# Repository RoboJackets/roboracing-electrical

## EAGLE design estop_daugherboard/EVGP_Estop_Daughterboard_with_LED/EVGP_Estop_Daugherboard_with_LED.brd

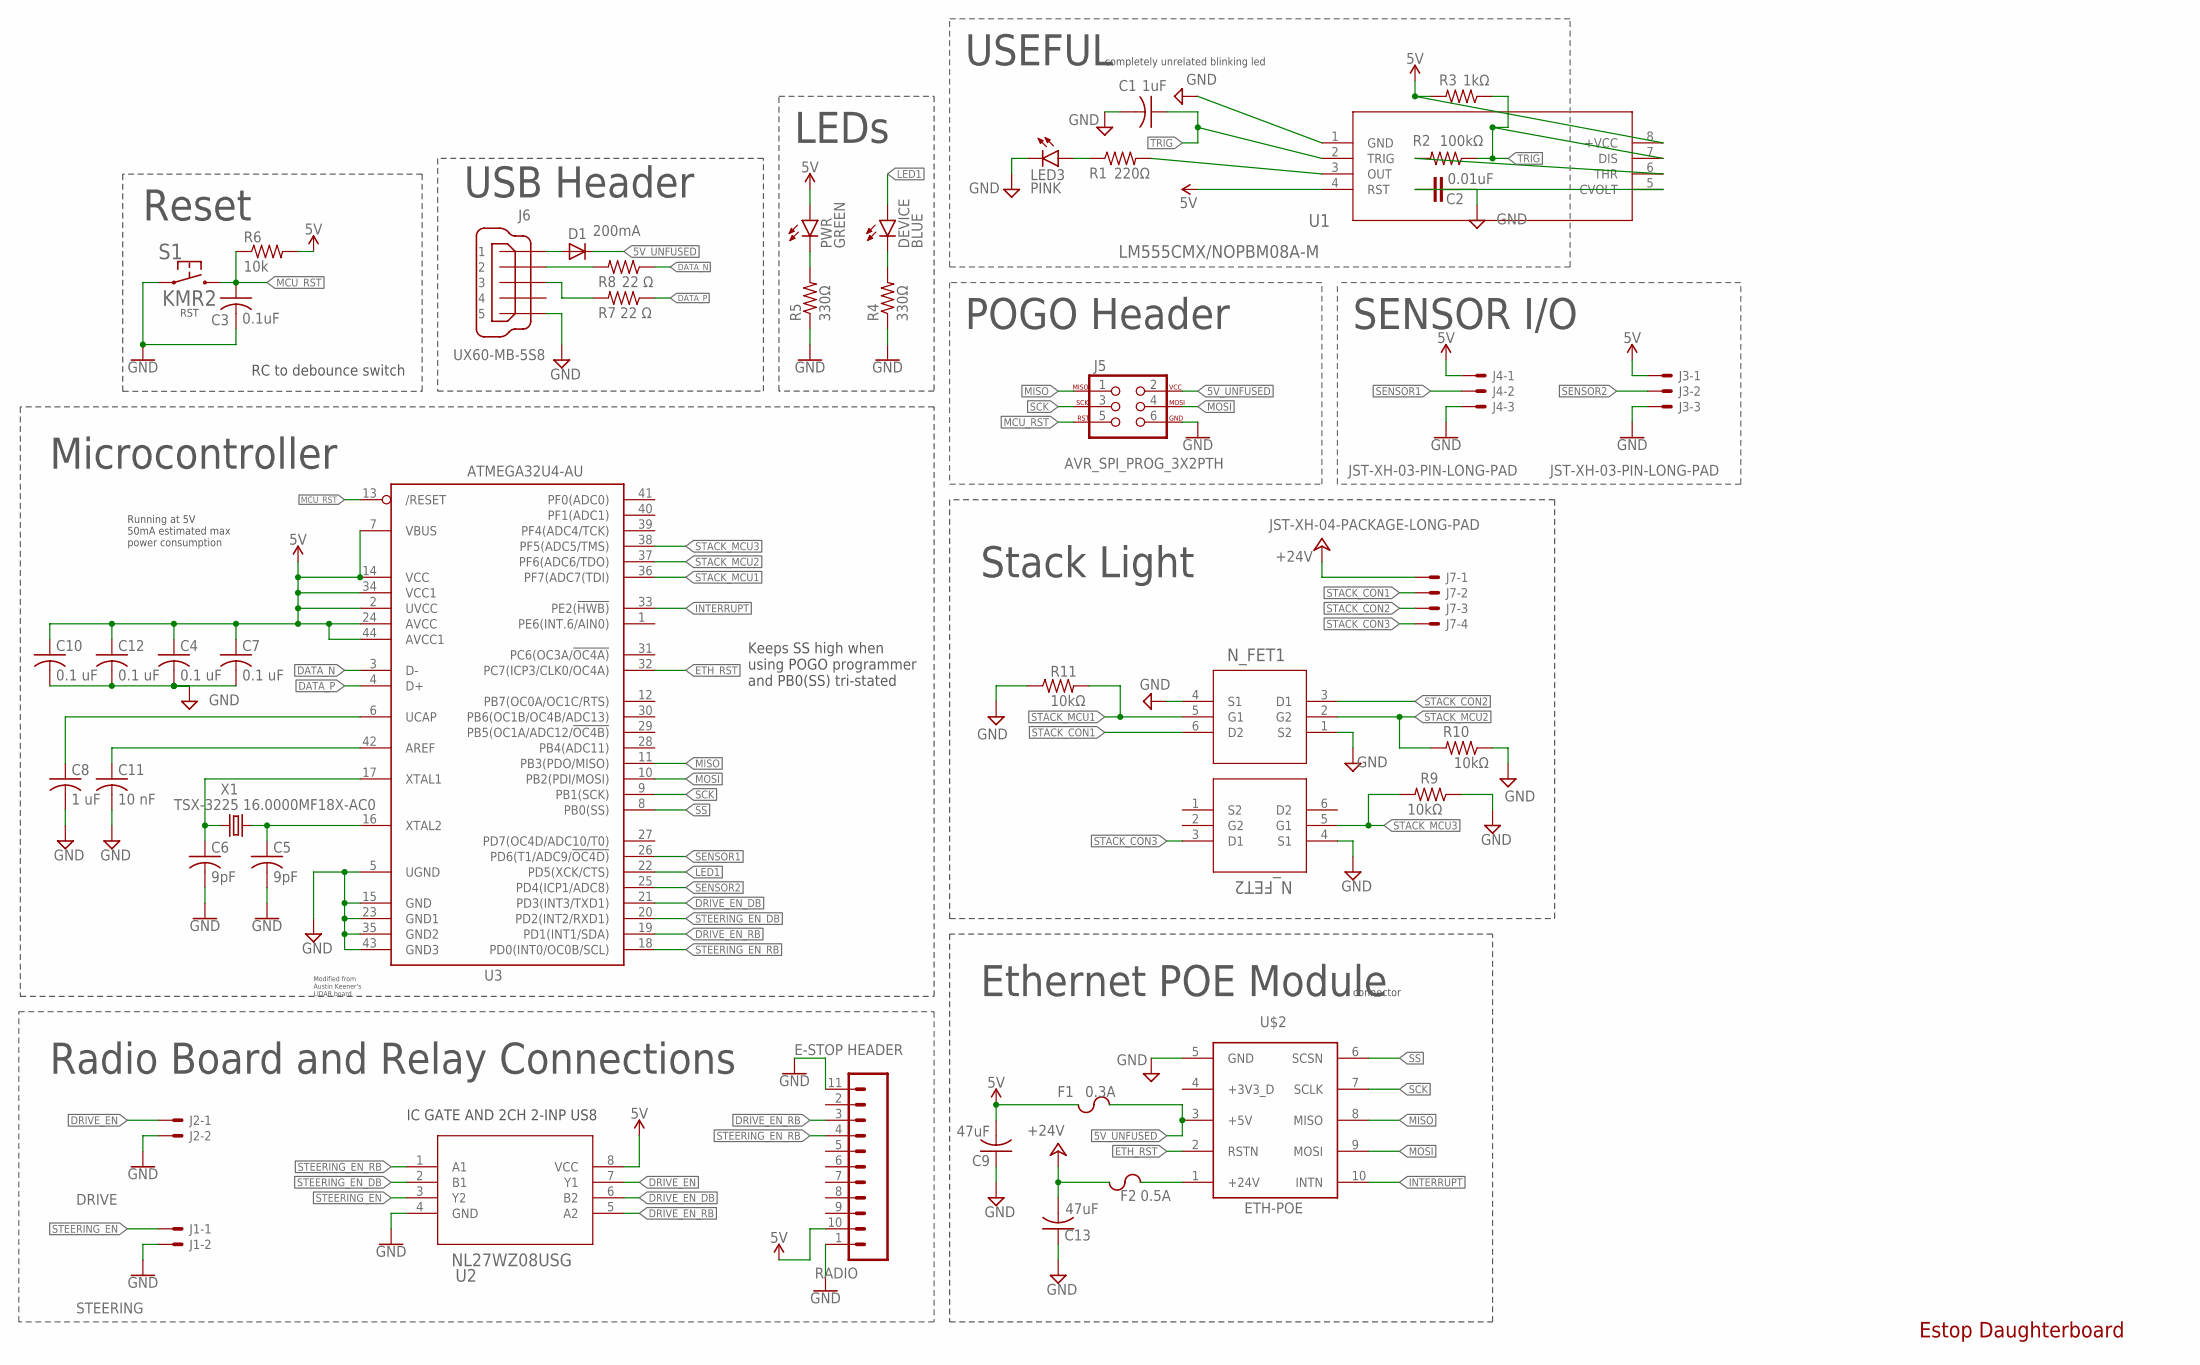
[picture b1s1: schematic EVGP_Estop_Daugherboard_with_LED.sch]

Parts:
C1: 1uF; C1206
C2: 0.01uF; C0603
C3: 0.1uF; C0603
C4, C7, C10, C12: 0.1 uF; C0603
C5, C6: 9pF; C0603
C8: 1 uF; C0603
C9, C13: 47uF; C1206
C11: 10 nF; C0603
D1: 200mA; SOD323-R
DEVICE: BLUE; CHIP-LED0603
F1: 0.3A; F1206
F2: 0.5A; F1206
J1: STEERING; JST-XH-02-PACKAGE-LONG-PAD
J2: DRIVE; JST-XH-02-PACKAGE-LONG-PAD
J3, J4: JST-XH-03-PIN-LONG-PAD; JST-XH-03-PACKAGE-LONG-PAD
J5: AVR_SPI_PROG_3X2PTH; 2X3
J6: UX60-MB-5S8
J7: JST-XH-04-PACKAGE-LONG-PAD
LED3: PINK; CHIP-LED0603
PWR: GREEN; CHIP-LED0603
Q1: N_FET2; SOT-363
Q2: N_FET1; SOT-363
R1: 220Ω; R0603
R2: 100kΩ; R0603
R3: 1kΩ; R0603
R4, R5: 330Ω; R0603
R6: 10k; R0603
R7, R8: 22 Ω; R0603
R9, R10, R11: 10kΩ; R0603
RADIO: E-STOP HEADER; RADIO_V1.3
S1: KMR2
U1: LM555CMX/NOPBM08A-M; M08A-M
U2: NL27WZ08USG; US8_2P40X2P10
U3: ATMEGA32U4-AU; TQFP44
U$2: ETH-POE; HDRVR10W64P4000X254_2X5_1016X508X254B
X1: TSX-3225 16.0000MF18X-AC0; XTAL-3.2X2.5

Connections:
5V: C4.1, C7.1, C9.2, C10.1, C12.1, F1.1, J3.1, J4.1, PWR.A, R3.2, R6.2, RADIO.10 (5V), U1.4 (RST), U1.8 (+VCC), U2.8 (VCC), U3.2 (UVCC), U3.7 (VBUS), U3.14 (VCC), U3.24 (AVCC), U3.34 (VCC1), U3.44 (AVCC1)
5V_UNFUSED: D1.C, F1.2, J5.2, U$2.3 (+5V)
24V_UNFUSED: F2.2, U$2.1 (+24V)
+24V: C13.2, F2.1, J7.1
AREF: C11.1, U3.42 (AREF)
DATA_N: R8.1, U3.3 (D-)
DATA_P: R7.1, U3.4 (D+)
DRIVE_EN: J2.1, U2.7 (Y1)
DRIVE_EN_DB: U2.6 (B2), U3.21 (PD3(INT3/TXD1))
DRIVE_EN_RB: RADIO.3 (D1), U2.5 (A2), U3.19 (PD1(INT1/SDA))
ETH_RST: U3.32 (PC7(ICP3/CLK0/OC4A)), U$2.2 (RSTN)
GND: C1.2, C2.2, C3.2, C4.2, C5.2, C6.2, C7.2, C8.2, C9.1, C10.2, C11.2, C12.2, C13.1, J1.2, J2.2, J3.3, J4.3, J5.6, J6.5, LED3.C, Q1.4 (S1), Q2.1 (S2), Q2.4 (S1), R4.1, R5.1, R9.1, R10.1, R11.1, RADIO.1 (GND), RADIO.11 (GND), S1.1.1 (1), S1.1.2 (1), U1.1 (GND), U2.4 (GND), U3.5 (UGND), U3.15 (GND), U3.23 (GND1), U3.35 (GND2), U3.43 (GND3), U$2.5 (GND)
INTERRUPT: U3.33 (PE2(!HWB)), U$2.10 (INTN)
LED1: DEVICE.A, U3.22 (PD5(XCK/CTS))
MCU_RST: C3.1, J5.5, R6.1, S1.2.1 (2), S1.2.2 (2), U3.13 (/RESET)
MISO: J5.1, U3.11 (PB3(PDO/MISO)), U$2.8 (MISO)
MOSI: J5.4, U3.10 (PB2(PDI/MOSI)), U$2.9 (MOSI)
unnamed: LED3.A, R1.1
unnamed: R2.2, U1.6 (THR)
unnamed: PWR.C, R5.2
unnamed: C2.1, U1.5 (CVOLT)
unnamed: J6.2, R8.2
unnamed: DEVICE.C, R4.2
unnamed: D1.A, J6.1
unnamed: R1.2, U1.3 (OUT)
unnamed: J6.3, R7.2
SCK: J5.3, U3.9 (PB1(SCK)), U$2.7 (SCLK)
SENSOR1: J4.2, U3.26 (PD6(T1/ADC9/!OC4D))
SENSOR2: J3.2, U3.25 (PD4(ICP1/ADC8))
SS: U3.8 (PB0(SS)), U$2.6 (SCSN)
STACK_CON1: J7.2, Q2.6 (D2)
STACK_CON2: J7.3, Q2.3 (D1)
STACK_CON3: J7.4, Q1.3 (D1)
STACK_MCU1: Q2.5 (G1), R11.2, U3.36 (PF7(ADC7(TDI))
STACK_MCU2: Q2.2 (G2), R10.2, U3.37 (PF6(ADC6/TDO))
STACK_MCU3: Q1.5 (G1), R9.2, U3.38 (PF5(ADC5/TMS))
STEERING_EN: J1.1, U2.3 (Y2)
STEERING_EN_DB: U2.2 (B1), U3.20 (PD2(INT2/RXD1))
STEERING_EN_RB: RADIO.4 (D2), U2.1 (A1), U3.18 (PD0(INT0/OC0B/SCL))
TRIG: C1.1, R2.1, R3.1, U1.2 (TRIG), U1.7 (DIS)
UCAP: C8.1, U3.6 (UCAP)
XTAL1: C6.1, U3.17 (XTAL1), X1.1
XTAL2: C5.1, U3.16 (XTAL2), X1.3 (2)

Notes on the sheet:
Modified from Austin Keener's LIDAR board
POGO Header
RC to debounce switch
Reset
LEDs
Running at 5V 50mA estimated max power consumption
Microcontroller
USB Header
Keeps SS high when using POGO programmer and PB0(SS) tri-stated
Radio Board and Relay Connections
IC GATE AND 2CH 2-INP US8
SENSOR I/O
Stack Light
Ethernet POE Module
connector
Estop Daughterboard
USEFUL
completely unrelated blinking led

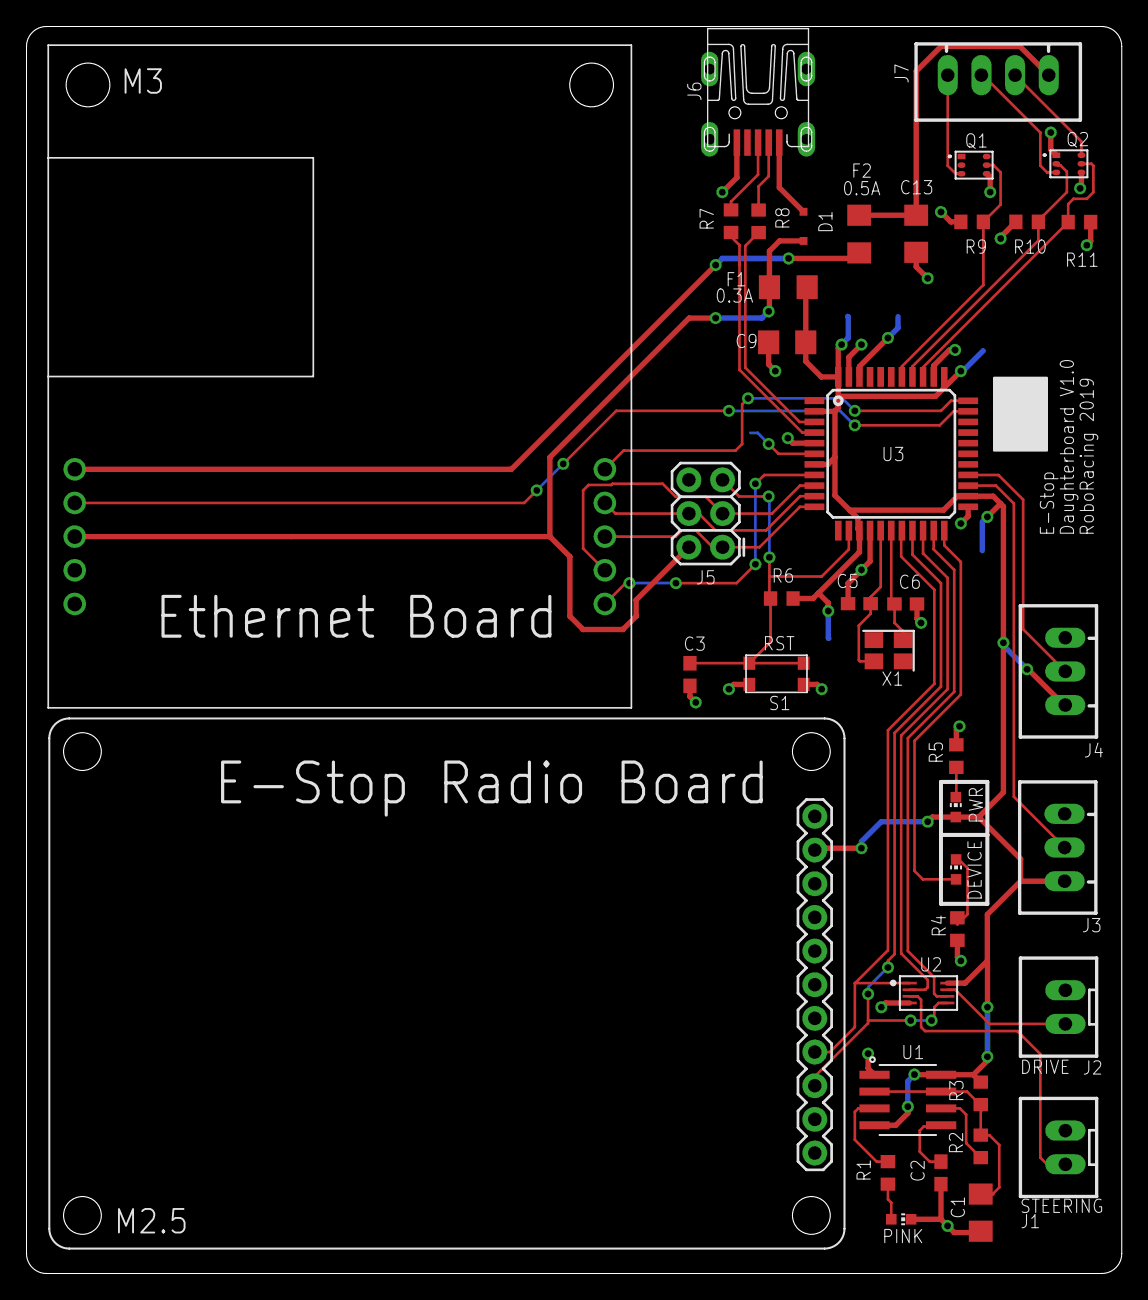
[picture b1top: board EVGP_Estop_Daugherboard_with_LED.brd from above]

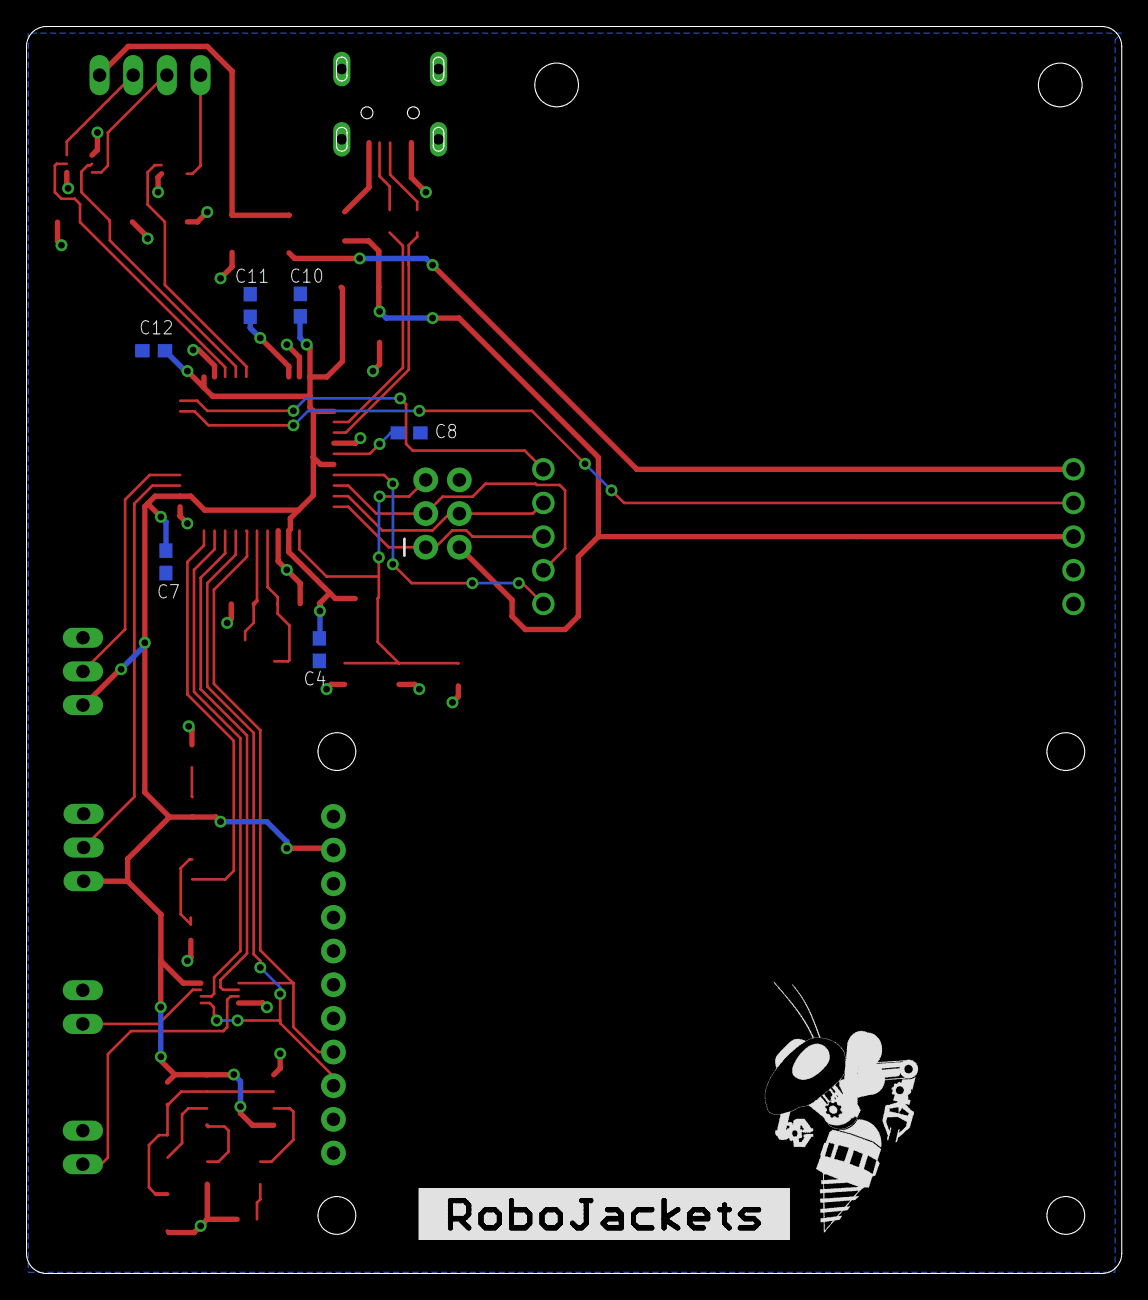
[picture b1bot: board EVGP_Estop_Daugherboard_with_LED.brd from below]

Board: 2 copper layers, 82.6 x 94.1 mm, 48 parts (8 on the bottom side), 43 nets.

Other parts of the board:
U$1: ROBOBUZZ_1.0X
U$3: ROBOJACKETS

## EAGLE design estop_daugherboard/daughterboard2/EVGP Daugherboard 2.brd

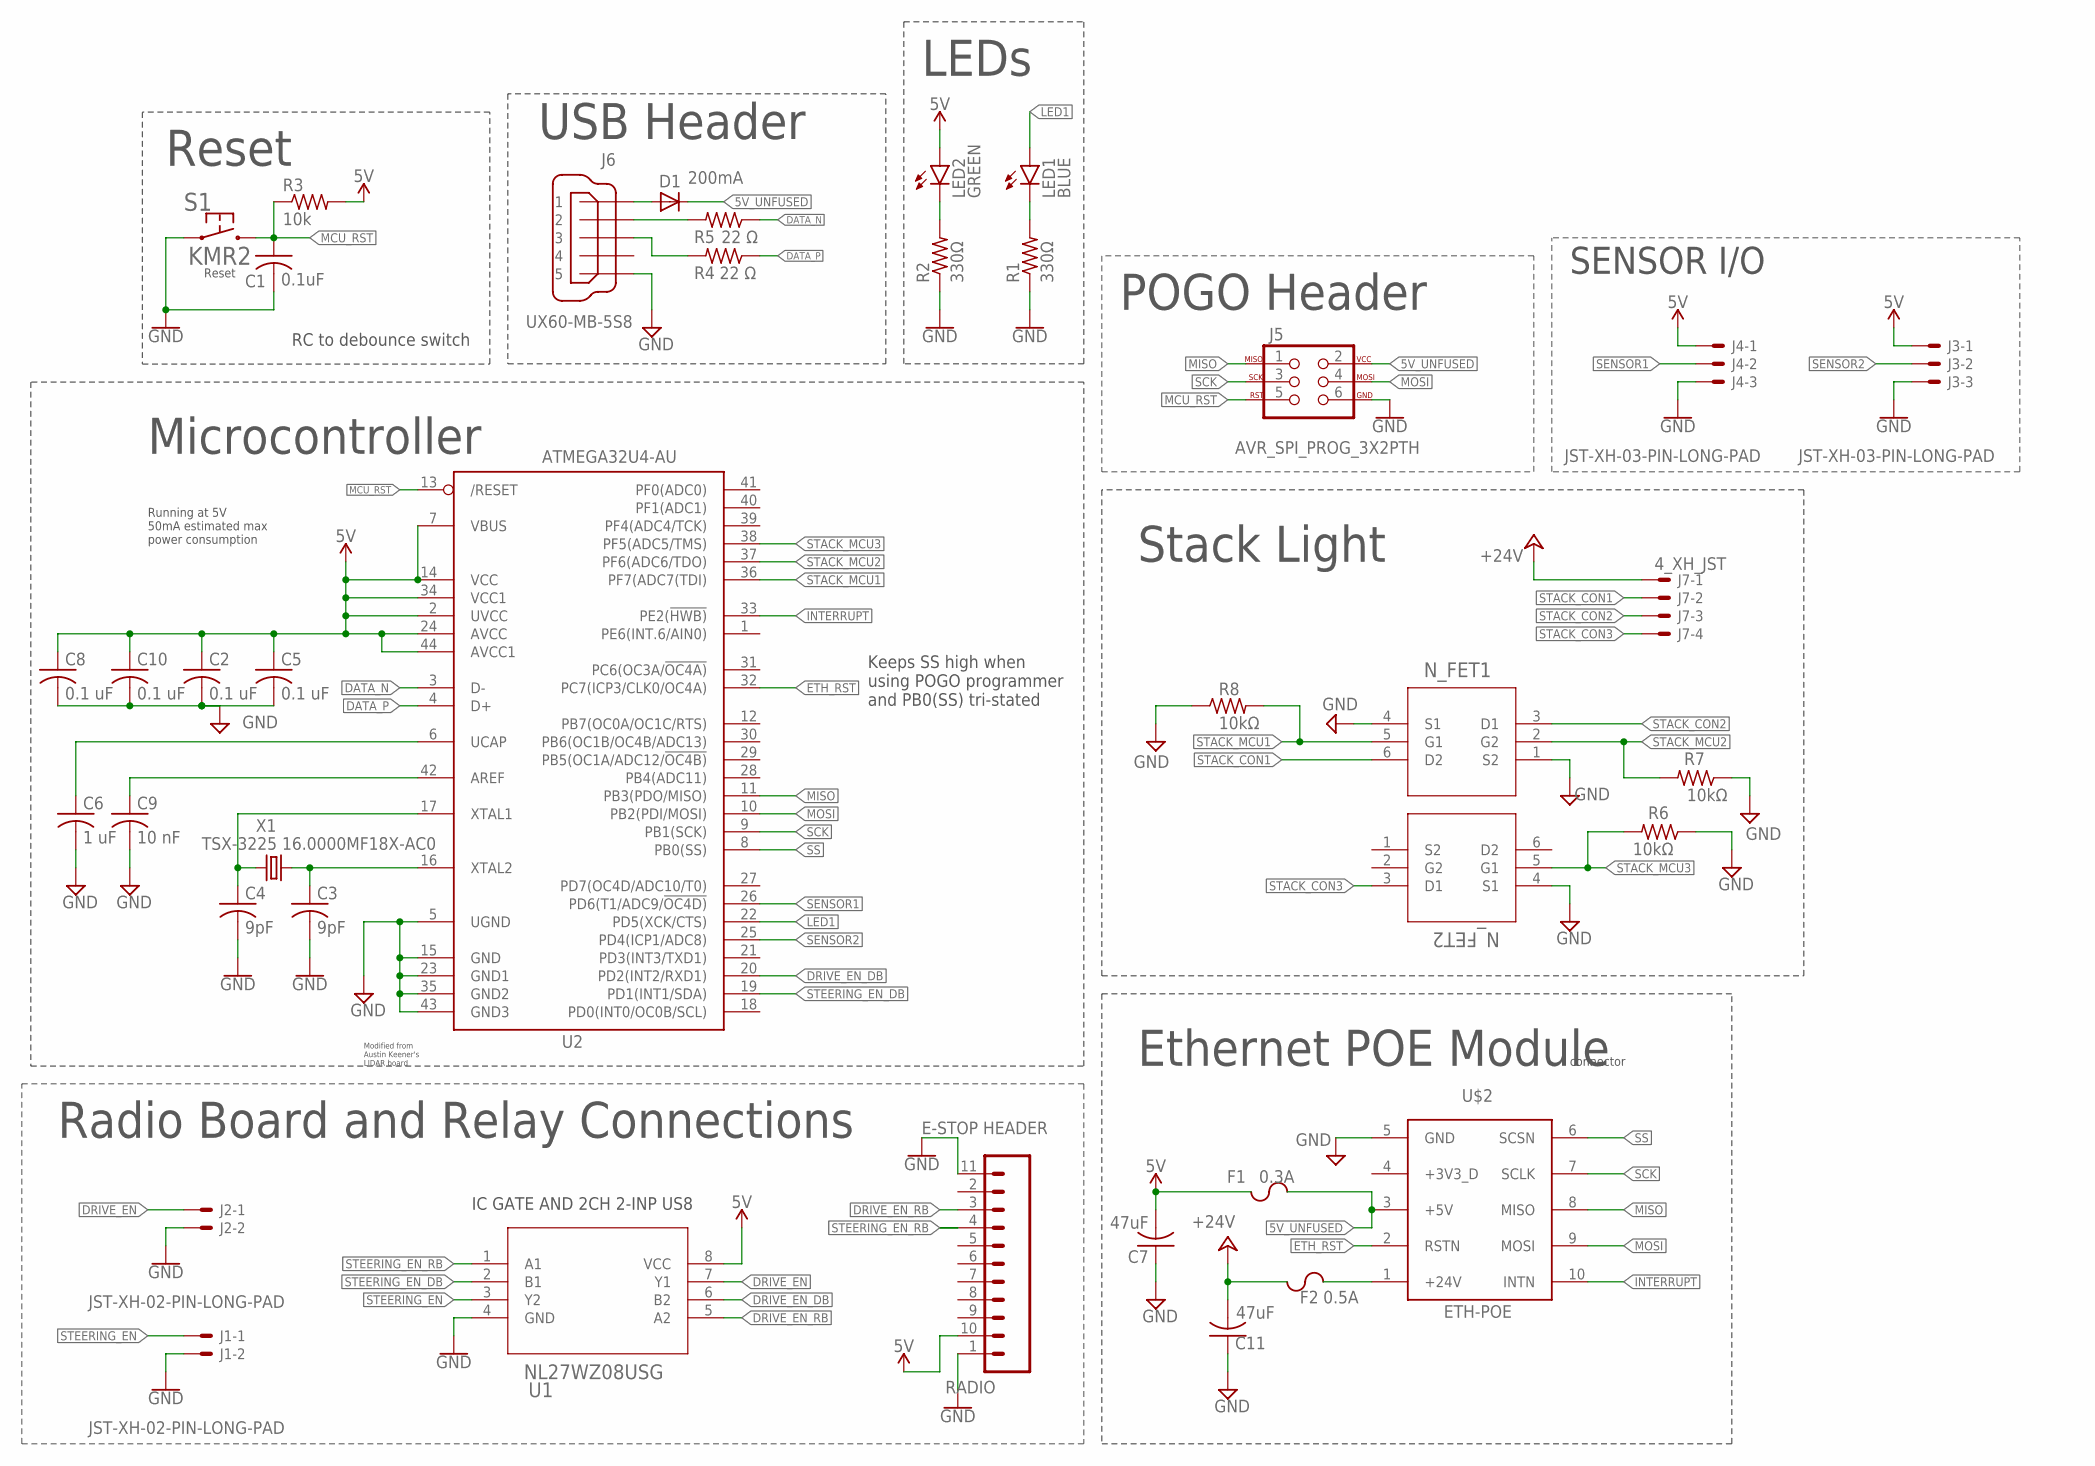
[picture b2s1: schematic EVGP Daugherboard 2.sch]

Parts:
C1: 0.1uF; C0603
C2, C5, C8, C10: 0.1 uF; C0603
C3, C4: 9pF; C0603
C6: 1 uF; C0603
C7, C11: 47uF; C1206
C9: 10 nF; C0603
D1: 200mA; SOD323-R
F1: 0.3A; F1206
F2: 0.5A; F1206
J1, J2: JST-XH-02-PIN-LONG-PAD; JST-XH-02-PACKAGE-LONG-PAD
J3, J4: JST-XH-03-PIN-LONG-PAD; JST-XH-03-PACKAGE-LONG-PAD
J5: AVR_SPI_PROG_3X2PTH; 2X3
J6: UX60-MB-5S8
J7: 4_XH_JST; JST-XH-04-PACKAGE-LONG-PAD
LED1: BLUE; CHIP-LED0603
LED2: GREEN; CHIP-LED0603
Q1: N_FET2; SOT-363
Q2: N_FET1; SOT-363
R1, R2: 330Ω; R0603
R3: 10k; R0603
R4, R5: 22 Ω; R0603
R6, R7, R8: 10kΩ; R0603
RADIO: E-STOP HEADER; RADIO_V1.3
S1: KMR2
U1: NL27WZ08USG; US8_2P40X2P10
U2: ATMEGA32U4-AU; TQFP44
U$2: ETH-POE; HDRVR10W64P4000X254_2X5_1016X508X254B
X1: TSX-3225 16.0000MF18X-AC0; XTAL-3.2X2.5

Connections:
5V: C2.1, C5.1, C7.2, C8.1, C10.1, F1.1, J3.1, J4.1, LED2.A, R3.2, RADIO.10 (5V), U1.8 (VCC), U2.2 (UVCC), U2.7 (VBUS), U2.14 (VCC), U2.24 (AVCC), U2.34 (VCC1), U2.44 (AVCC1)
5V_UNFUSED: D1.C, F1.2, J5.2, U$2.3 (+5V)
24V_UNFUSED: F2.2, U$2.1 (+24V)
+24V: C11.2, F2.1, J7.1
AREF: C9.1, U2.42 (AREF)
DATA_N: R5.1, U2.3 (D-)
DATA_P: R4.1, U2.4 (D+)
DRIVE_EN: J2.1, U1.7 (Y1)
DRIVE_EN_DB: U1.6 (B2), U2.20 (PD2(INT2/RXD1))
DRIVE_EN_RB: RADIO.3 (D1), U1.5 (A2)
ETH_RST: U2.32 (PC7(ICP3/CLK0/OC4A)), U$2.2 (RSTN)
GND: C1.2, C2.2, C3.2, C4.2, C5.2, C6.2, C7.1, C8.2, C9.2, C10.2, C11.1, J1.2, J2.2, J3.3, J4.3, J5.6, J6.5, Q1.4 (S1), Q2.1 (S2), Q2.4 (S1), R1.1, R2.1, R6.1, R7.1, R8.1, RADIO.1 (GND), RADIO.11 (GND), S1.1.1 (1), S1.1.2 (1), U1.4 (GND), U2.5 (UGND), U2.15 (GND), U2.23 (GND1), U2.35 (GND2), U2.43 (GND3), U$2.5 (GND)
INTERRUPT: U2.33 (PE2(!HWB)), U$2.10 (INTN)
LED1: LED1.A, U2.22 (PD5(XCK/CTS))
MCU_RST: C1.1, J5.5, R3.1, S1.2.1 (2), S1.2.2 (2), U2.13 (/RESET)
MISO: J5.1, U2.11 (PB3(PDO/MISO)), U$2.8 (MISO)
MOSI: J5.4, U2.10 (PB2(PDI/MOSI)), U$2.9 (MOSI)
unnamed: LED2.C, R2.2
unnamed: J6.2, R5.2
unnamed: LED1.C, R1.2
unnamed: D1.A, J6.1
unnamed: J6.3, R4.2
SCK: J5.3, U2.9 (PB1(SCK)), U$2.7 (SCLK)
SENSOR1: J4.2, U2.26 (PD6(T1/ADC9/!OC4D))
SENSOR2: J3.2, U2.25 (PD4(ICP1/ADC8))
SS: U2.8 (PB0(SS)), U$2.6 (SCSN)
STACK_CON1: J7.2, Q2.6 (D2)
STACK_CON2: J7.3, Q2.3 (D1)
STACK_CON3: J7.4, Q1.3 (D1)
STACK_MCU1: Q2.5 (G1), R8.2, U2.36 (PF7(ADC7(TDI))
STACK_MCU2: Q2.2 (G2), R7.2, U2.37 (PF6(ADC6/TDO))
STACK_MCU3: Q1.5 (G1), R6.2, U2.38 (PF5(ADC5/TMS))
STEERING_EN: J1.1, U1.3 (Y2)
STEERING_EN_DB: U1.2 (B1), U2.19 (PD1(INT1/SDA))
STEERING_EN_RB: RADIO.4 (D2), U1.1 (A1)
UCAP: C6.1, U2.6 (UCAP)
XTAL1: C4.1, U2.17 (XTAL1), X1.1
XTAL2: C3.1, U2.16 (XTAL2), X1.3 (2)

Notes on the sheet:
Modified from Austin Keener's LIDAR board
POGO Header
RC to debounce switch
Reset
LEDs
Running at 5V 50mA estimated max power consumption
Microcontroller
USB Header
Keeps SS high when using POGO programmer and PB0(SS) tri-stated
Radio Board and Relay Connections
IC GATE AND 2CH 2-INP US8
SENSOR I/O
Stack Light
Ethernet POE Module
connector

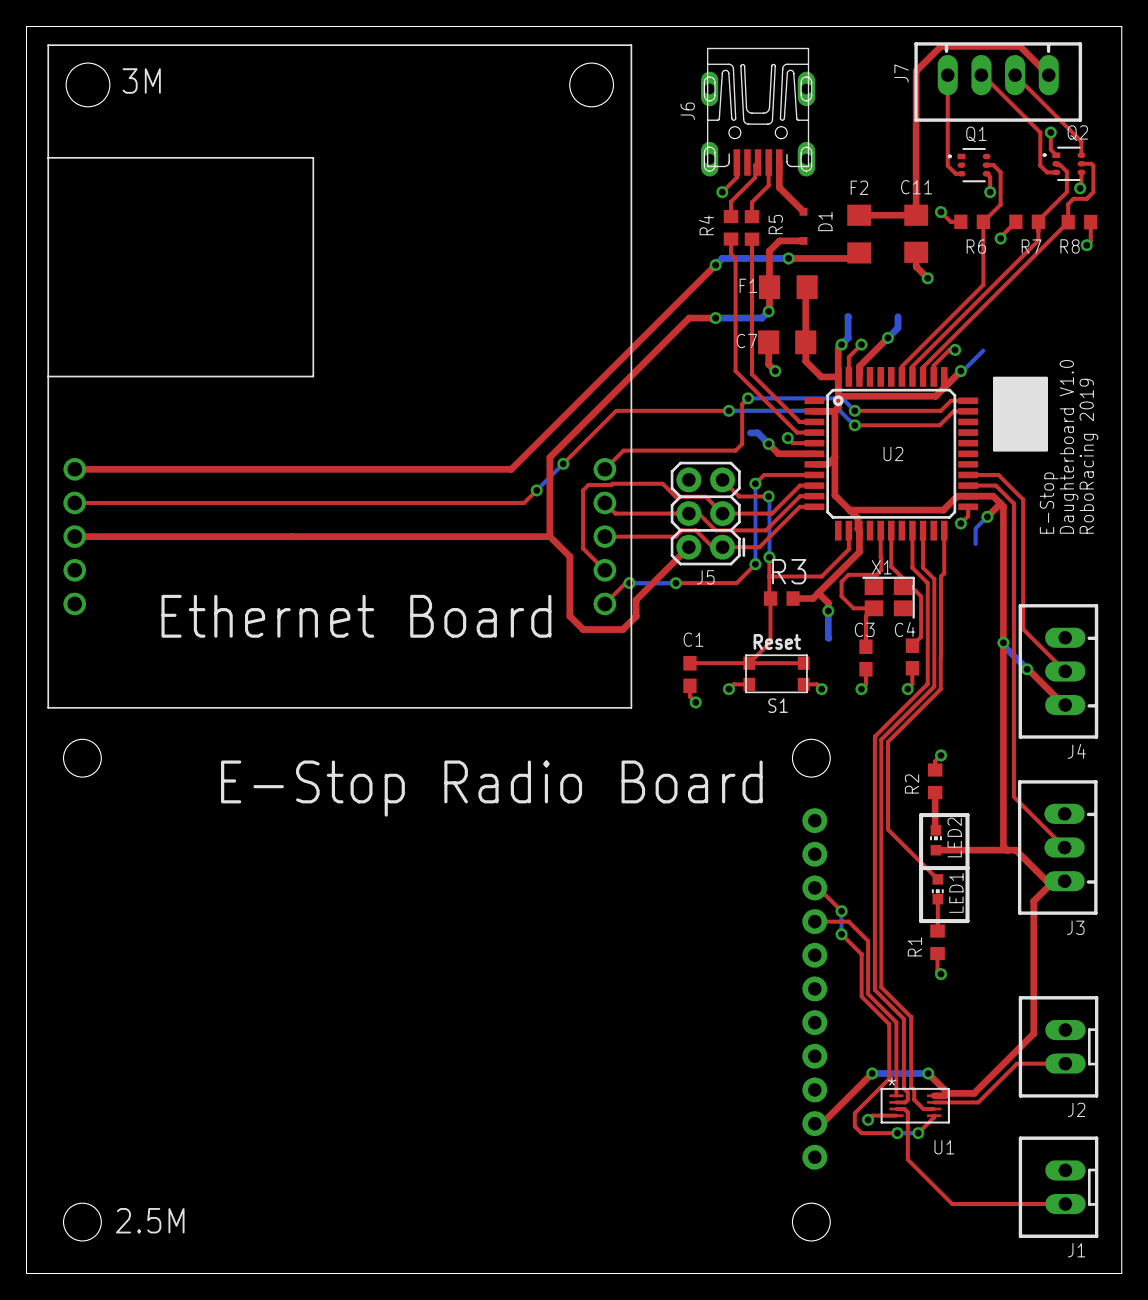
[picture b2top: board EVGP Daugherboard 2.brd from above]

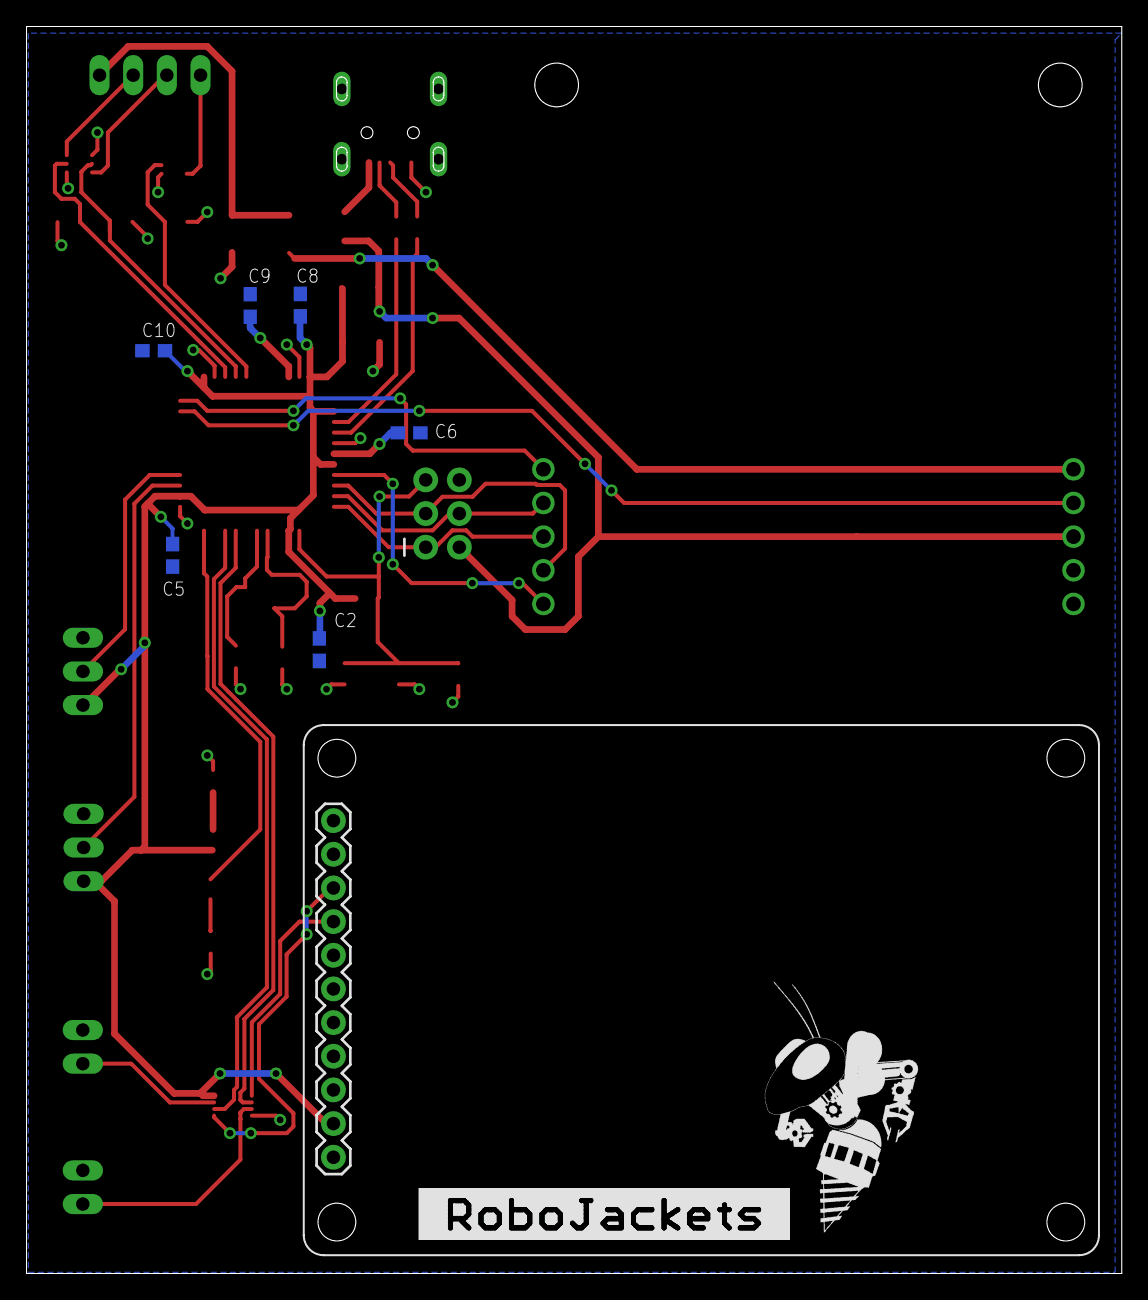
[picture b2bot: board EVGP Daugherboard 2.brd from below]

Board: 2 copper layers, 82.6 x 94.1 mm, 41 parts (9 on the bottom side), 38 nets.

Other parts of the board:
U$1: ROBOBUZZ_1.0X
U$3: ROBOJACKETS

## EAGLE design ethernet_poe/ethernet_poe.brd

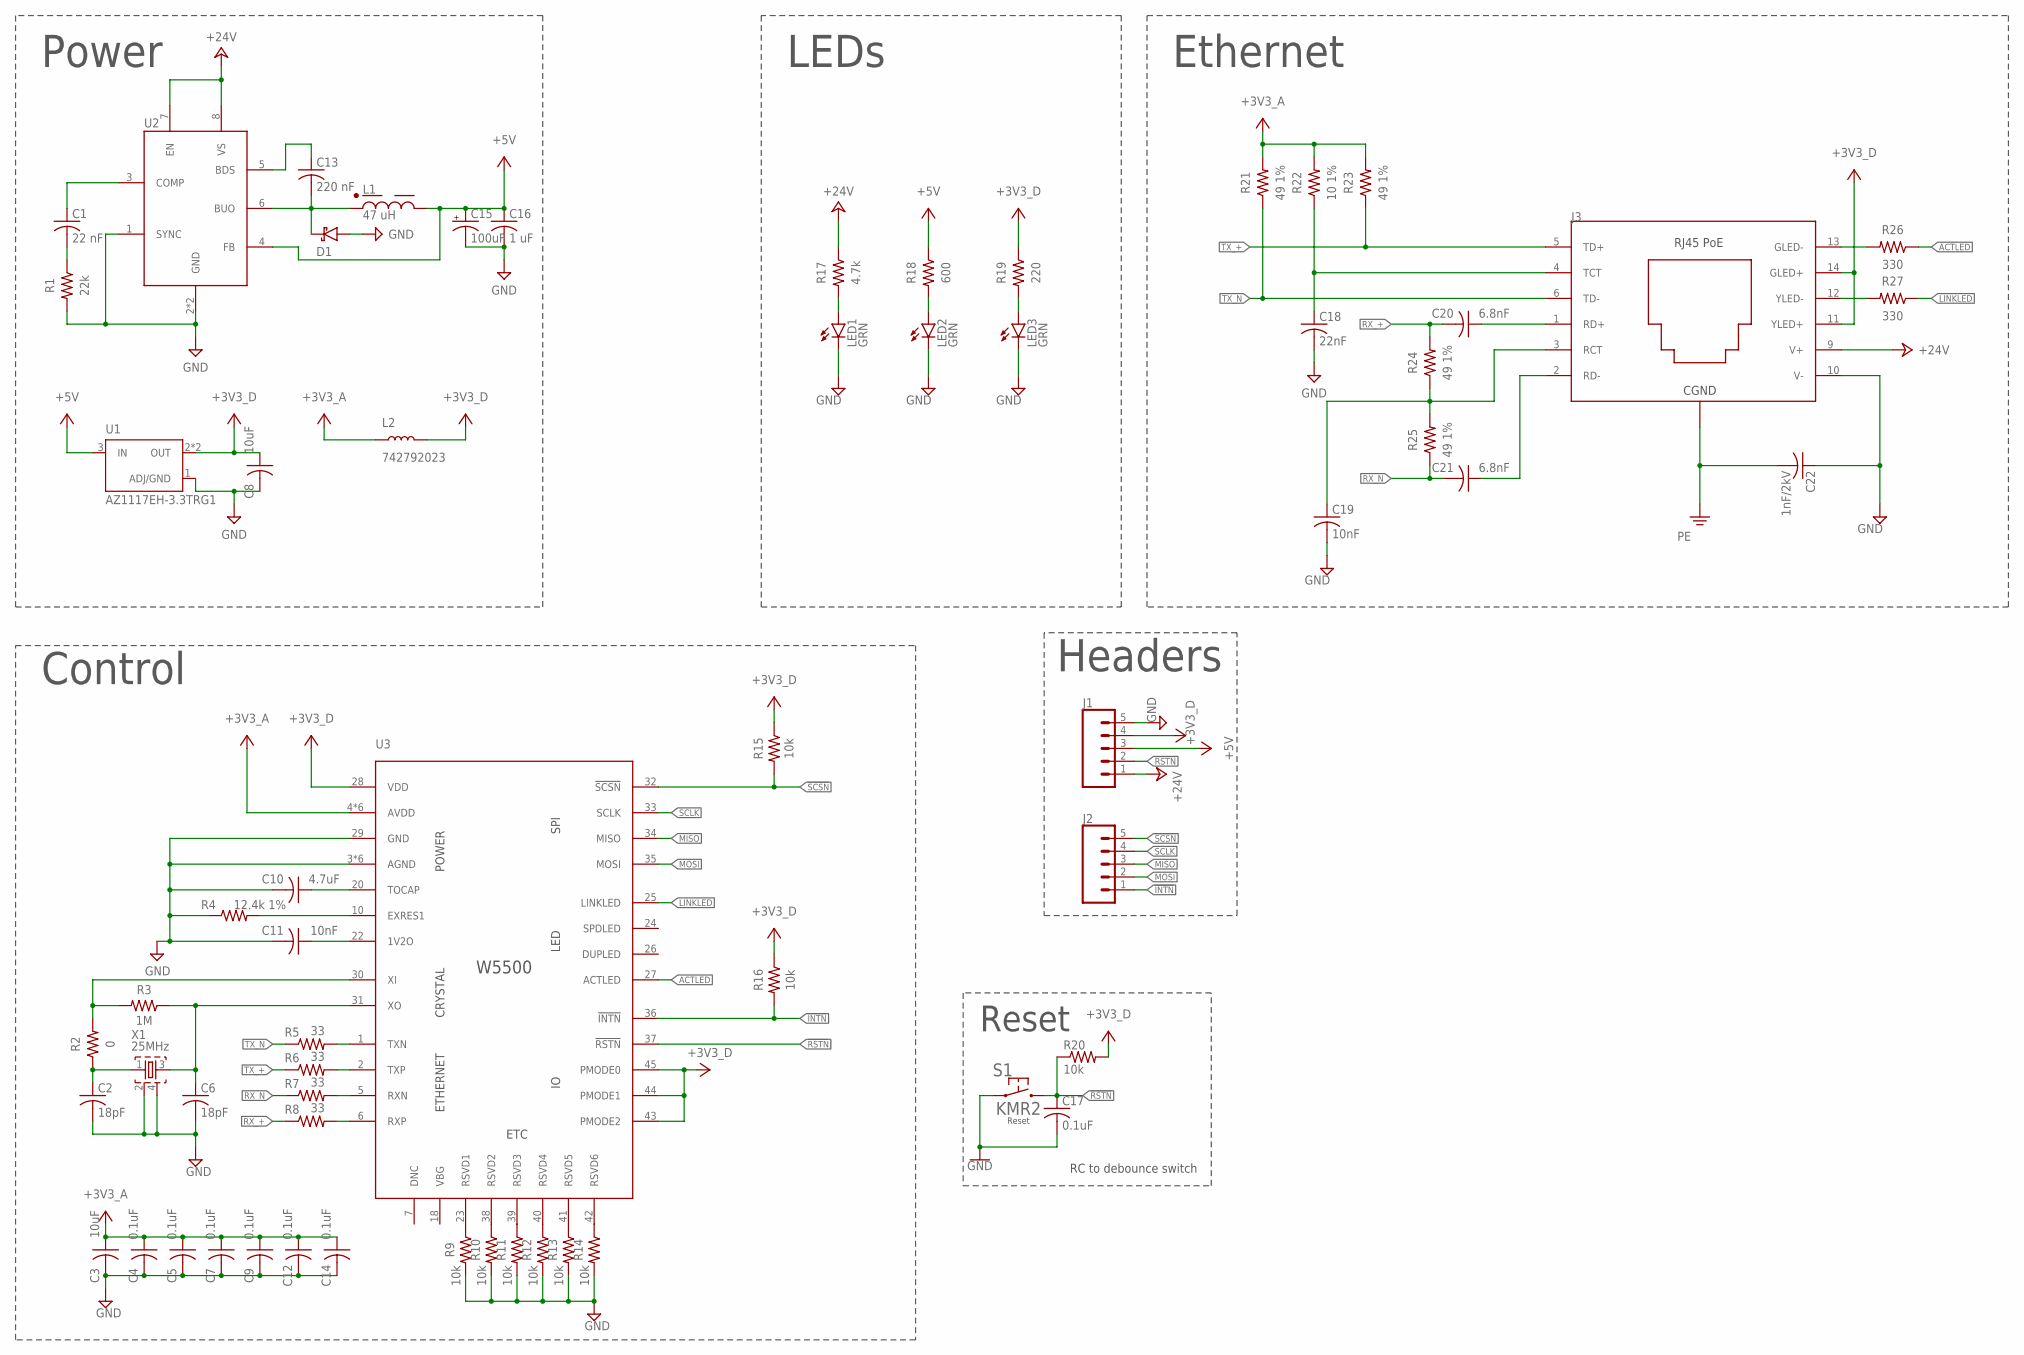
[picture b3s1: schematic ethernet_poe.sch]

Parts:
C1: 22 nF; C0603
C2, C6: 18pF; C0603
C3, C8: 10uF; C0603
C4, C5, C7, C9, C12, C14, C17: 0.1uF; C0603
C10: 4.7uF; C0603
C11, C19: 10nF; C0603
C13: 220 nF; C0603
C15: 100uF; E2-5
C16: 1 uF; C0603
C18: 22nF; C0603
C20, C21: 6.8nF; C0603
C22: 1nF/2kV; C1206
D1: SCHOTTKYSOD-323; SOD-323
J1, J2: CONN_05; 1X05
J3: ARJP11A; ARJP11A-MBSB-A-B-EMU2
L1: 47 uH; 744771147
L2: 742792023; 0805
LED1, LED2, LED3: GRN; CHIP-LED0603
R1: 22k; R0603
R2: 0; R0603
R3: 1M; R0603
R4: 12.4k 1%; R0603
R5, R6, R7, R8: 33; R0603
R9, R10, R11, R12, R13, R14, R15, R16, R20: 10k; R0603
R17: 4.7k; R0603
R18: 600; R0603
R19: 220; R0603
R21, R23, R24, R25: 49 1%; R0603
R22: 10 1%; R0603
R26, R27: 330; R0603
S1: KMR2
U1: AZ1117EH-3.3TRG1; SOT230P700X180-4N
U2: IFX91041; SOIC-8-EXPOSED_PAD
U3: W5500; 48-LQFP
X1: 25MHz; OSCILLATOR-SMD-2.5X2

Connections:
3V3_LED: LED3.A, R19.2
5V_LED: LED2.A, R18.2
24V_LED: LED1.A, R17.2
!INTN: J2.1, R16.2, U3.36 (!INTN)
!RSTN: C17.1, J1.2, R20.1, S1.2.1 (2), S1.2.2 (2), U3.37 (!RSTN)
!SCSN: J2.5, R15.2, U3.32 (!SCSN)
+3V3_A: C3.1, C4.1, C5.1, C7.1, C9.1, C12.1, C14.1, L2.1, R21.2, R22.2, R23.2, U3.4 (AVDD), U3.8 (AVDD), U3.11 (AVDD), U3.15 (AVDD), U3.17 (AVDD), U3.21 (AVDD)
+3V3_D: C8.1, J1.4, J3.11 (YLED+), J3.14 (GLED+), L2.2, R15.1, R16.1, R19.1, R20.2, U1.2 (OUT), U1.4 (OUT), U3.28 (VDD), U3.43 (PMODE2), U3.44 (PMODE1), U3.45 (PMODE0)
+5V: C15.+, C16.1, J1.3, L1.1, R18.1, U1.3 (IN), U2.4 (FB)
+24V: J1.1, J3.9 (V+), R17.1, U2.7 (EN), U2.8 (VS)
ACTLED: R26.1, U3.27 (ACTLED)
GND: C2.2, C3.2, C4.2, C5.2, C6.2, C7.2, C8.2, C9.2, C10.2, C11.2, C12.2, C14.2, C15.-, C16.2, C17.2, C18.2, C19.2, C22.1, D1.A, J1.5, J3.10 (V-), LED1.C, LED2.C, LED3.C, R1.2, R4.1, R9.2, R10.2, R11.2, R12.2, R13.2, R14.2, S1.1.1 (1), S1.1.2 (1), U1.1 (ADJ/GND), U2.1 (SYNC), U2.2 (GND), U2.P$9 (GND), U3.3 (AGND), U3.9 (AGND), U3.14 (AGND), U3.16 (AGND), U3.19 (AGND), U3.29 (GND), U3.48 (AGND), X1.2 (SHD1), X1.4 (SHD2)
LINKLED: R27.1, U3.25 (LINKLED)
MISO: J2.3, U3.34 (MISO)
MOSI: J2.2, U3.35 (MOSI)
unnamed: R9.1, U3.23 (RSVD1)
unnamed: R10.1, U3.38 (RSVD2)
unnamed: R11.1, U3.39 (RSVD3)
unnamed: R5.2, U3.1 (TXN)
unnamed: R6.2, U3.2 (TXP)
unnamed: R12.1, U3.40 (RSVD4)
unnamed: R7.2, U3.5 (RXN)
unnamed: R8.2, U3.6 (RXP)
unnamed: C2.1, R2.1, X1.1 (IN)
unnamed: J3.12 (YLED-), R27.2
unnamed: C6.1, R3.1, U3.31 (XO), X1.3 (OUT)
unnamed: J3.13 (GLED-), R26.2
unnamed: R2.2, R3.2, U3.30 (XI)
unnamed: C13.2, D1.C, L1.P$2, U2.6 (BUO)
unnamed: C13.1, U2.5 (BDS)
unnamed: C1.2, R1.1
unnamed: C1.1, U2.3 (COMP)
unnamed: C11.1, U3.22 (1V2O)
unnamed: C10.1, U3.20 (TOCAP)
unnamed: R13.1, U3.41 (RSVD5)
unnamed: R4.2, U3.10 (EXRES1)
unnamed: R14.1, U3.42 (RSVD6)
PE: C22.2, J3.15 (CGND), J3.16 (CGND)
RCT: C19.1, J3.3 (RCT), R24.1, R25.2
RD_+: C20.1, J3.1 (RD+)
RD_N: C21.1, J3.2 (RD-)
RX_+: C20.2, R8.1, R24.2
RX_N: C21.2, R7.1, R25.1
SCLK: J2.4, U3.33 (SCLK)
TCT: C18.1, J3.4 (TCT), R22.1
TX_+: J3.5 (TD+), R6.1, R23.1
TX_N: J3.6 (TD-), R5.1, R21.1

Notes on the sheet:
Power
Control
LEDs
Ethernet
Headers
RC to debounce switch
Reset

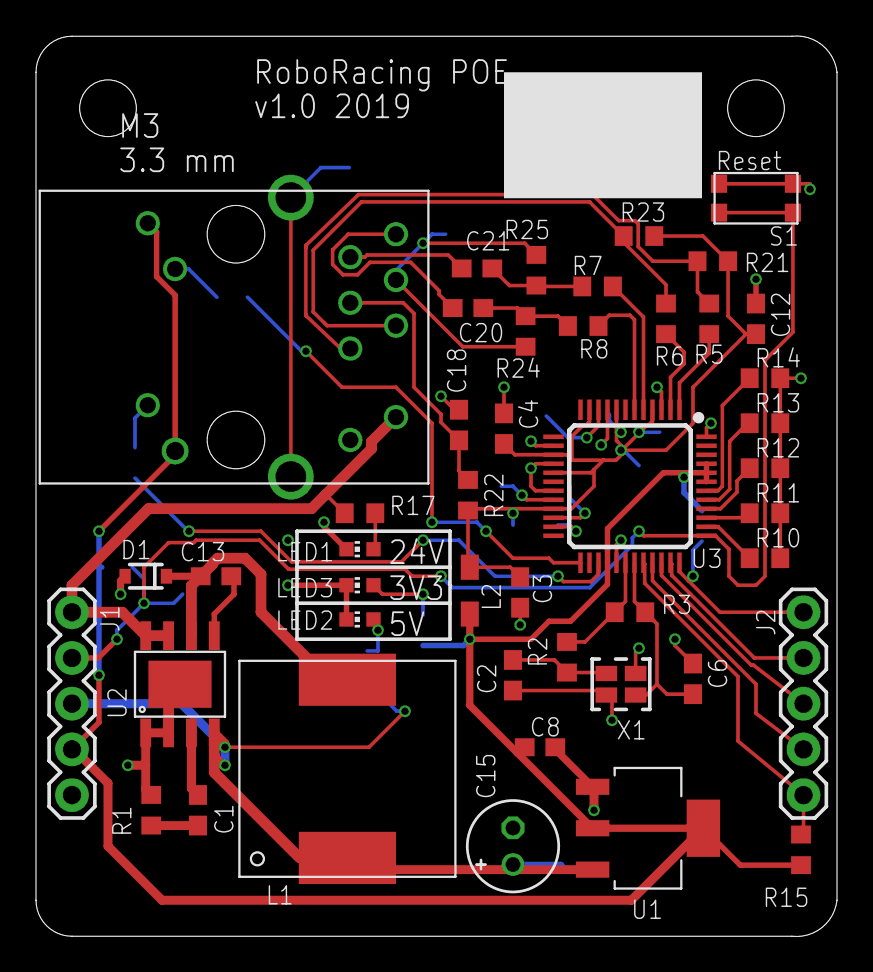
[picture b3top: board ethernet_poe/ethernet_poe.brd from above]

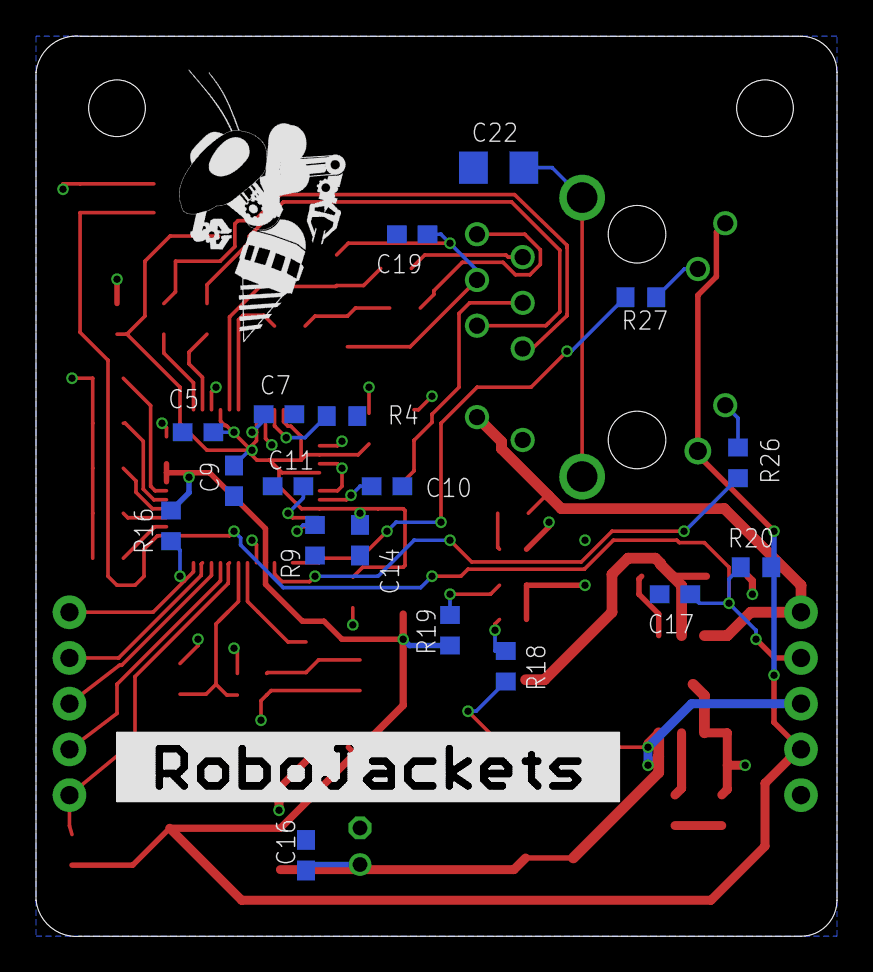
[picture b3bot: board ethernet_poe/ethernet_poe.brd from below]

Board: 2 copper layers, 44.5 x 50.0 mm, 65 parts (20 on the bottom side), 47 nets.

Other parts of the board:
U$1: ROBOJACKETS
U$2: ROBOBUZZ_0.8X

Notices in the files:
parts and their libraries:
SparkFun-Connectors: Licensing: Creative Commons ShareAlike 4.0 International - https://creativecommons.org/licenses/by-sa/4.0
COPYRIGHT: Copyright (C) 2018 Accelerated Designs. All rights reserved
Wurth_Electronic_Inductors: Copyright: Würth Elektronik
